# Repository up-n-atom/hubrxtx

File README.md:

# hubrxtx
Home Hub 4000 / Giga Hub serial USB jig

<a href="https://oshpark.com/shared_projects/M0UZDN4L"></img></a>

# Bill of Materials

## Required

| Ref.               | Value        | [LCSC](https://www.lcsc.com/) | [AliExpress](https://www.aliexpress.com) | Qty. |
| --                 | --           | --                            | --                                       | --:  |
| C3                 | 0.1 uF       | [C2930551](https://www.lcsc.com/product-detail/Multilayer-Ceramic-Capacitors-MLCC-SMD-SMT_YAGEO-CC0603KRX5R8BB104_C2930551.html)   |  | 1    |
| U1                 | CH340K       | [C18208922](https://www.lcsc.com/product-detail/USB-Converters_WCH-Jiangsu-Qin-Heng-CH340K_C18208922.html) | <https://s.click.aliexpress.com/e/_mKKYYbw> | 1    |
| J1                 | USB B Micro  | [C145795](https://www.lcsc.com/product-detail/USB-Connectors_Korean-Hroparts-Elec-U-D-M5DD-W-1_C145795.html) | <https://s.click.aliexpress.com/e/_mMzctcY> | 1    |
| TP1, TP2, TP3, TP4 | P100-H2      |  | <https://s.click.aliexpress.com/e/_mO8N2oG> | 4    |
| Plastic Rivet | R4060        |  | <https://a.aliexpress.com/_m0u7X0g>         | 2    |

## Optional - LEDs

| Ref.               | Value        | [LCSC](https://www.lcsc.com/) | Qty. |
| --                 | --           | --                            | --:  |
| R1              | 220 Ohm      | [C304718](https://www.lcsc.com/product-detail/Chip-Resistor-Surface-Mount_FH-Guangdong-Fenghua-Advanced-Tech-RS-03K2200FT_C304718.html) | 1 |
| R2, R3          | 22 Ohm       | [C2907129](https://www.lcsc.com/product-detail/Chip-Resistor-Surface-Mount_FOJAN-FRC0603J220-TS_C2907129.html) | 2 |
| D1              | Red          | [C965799](https://www.lcsc.com/product-detail/span-style-background-color-ff0-LED-span-Indication-Discrete_XINGLIGHT-XL-1608SURC-06_C965799.html) | 1 |
| D2              | White        | [C965808](https://www.lcsc.com/product-detail/LED-Indication-Discrete_XINGLIGHT-XL-1608UWC-04_C965808.html) | 1 |
| D3              | Blue         | [C965807](https://www.lcsc.com/product-detail/LED-Indication-Discrete_XINGLIGHT-XL-1608UBC-04_C965807.html) | 1 |

## Optional - USB power

| Ref.            | Value        | [LCSC](https://www.lcsc.com/) | Qty. |
| --              | --           | --                            | --:  |
| C1, C2          | 1.0 uF       | [C7503503](https://www.lcsc.com/product-detail/Multilayer-Ceramic-Capacitors-MLCC-SMD-SMT_HRE-CGA0603X7R105K250JT_C7503503.html) | 2    |
| F1              | 200 mA       | [C210356](https://www.lcsc.com/product-detail/Resettable-Fuses_BOURNS-MF-FSMF020X-2_C210356.html) | 1    |
| U2              | XC6206P332MR | [C5148692](https://www.lcsc.com/product-detail/Voltage-Regulators-Linear-Low-Drop-Out-LDO-Regulators_HXY-MOSFET-XC6206P332MR_C5148692.html) | 1 |

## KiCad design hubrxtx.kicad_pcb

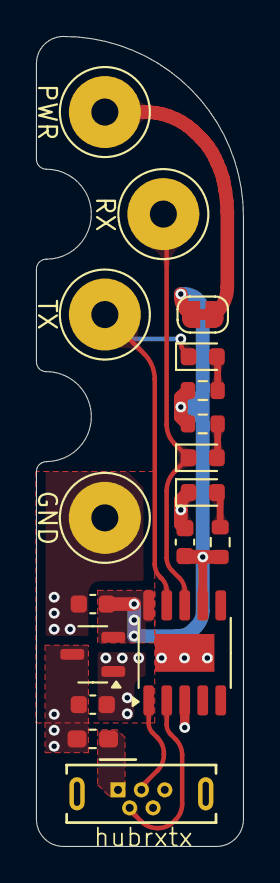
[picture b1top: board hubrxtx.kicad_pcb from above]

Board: 2 copper layers, 11.5 x 45.0 mm, 18 parts (0 on the bottom side), 12 nets.

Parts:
C1, C2: 1uF; C_0603_1608Metric
C3: 0.1uF; C_0603_1608Metric
D1: RED; LED_0603_1608Metric
D2: WHITE; LED_0603_1608Metric
D3: BLUE; LED_0603_1608Metric
F1: 200mA; Fuse_0603_1608Metric_Pad1.05x0.95mm_HandSolder
J1: USB_B_Micro; USB_Micro-B_Wuerth_614105150721_Vertical
JP1: power; SolderJumper-2_P1.3mm_Bridged_RoundedPad1.0x1.5mm
R1: 220Ω; R_0603_1608Metric
R2, R3: 22Ω; R_0603_1608Metric
TP1: PWR; TestPoint_Pad_D4.0mm
TP2: RX; TestPoint_Pad_D4.0mm
TP3: TX; TestPoint_Pad_D4.0mm
TP4: GND; TestPoint_Pad_D4.0mm
U1: CH340K; SSOP-10-1EP_3.9x4.9mm_P1mm_EP2.1x3.3mm
U2: XC6206PxxxMR; SOT-23-3

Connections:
GND: C1.2, C2.2, C3.1, D1.1 (K), J1.5 (GND), J1.6 (Shield), TP4.1, U1.3 (GND), U1.11 (GND), U2.1 (GND)
unnamed: D1.2 (A), R1.1
unnamed: D2.2 (A), R2.1
unnamed: D3.2 (A), R3.1
unnamed: J1.3 (D+), U1.1 (UD+)
unnamed: J1.2 (D-), U1.2 (UD-)
unnamed: F1.1, J1.1 (VBUS)
unnamed: JP1.2 (B), TP1.1
unnamed: D3.1 (K), TP3.1, U1.9 (RXD)
unnamed: D2.1 (K), TP2.1, U1.8 (TXD)
VBUS: C1.1, F1.2, U2.3 (VI)
VCC: C2.1, C3.2, JP1.1 (A), R1.2, R2.2, R3.2, U1.7 (VCC), U1.10 (V3), U2.2 (VO)

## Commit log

2024-09-08 Add KiCAD project files
2024-09-08 README: Add render
2024-09-22 README: Add demonstration image
2024-09-22 README: Add OSHPark project link
2024-09-23 Update KiCad project
    * Cleanup schematic
    * Add net classes
2024-09-23 README: Add BOM
2024-09-23 README: Add rivet link
